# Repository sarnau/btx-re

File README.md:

# btx-re — Commodore BTX Decoder II firmware reverse engineering

Reconstructs a commented, byte-identical assembly listing of the Commodore
Bildschirmtext Decoder II ROM (`c64_btx_decoder_ii.bin`, MC6801, 32 KB at
`$8000`–`$FFFF`).

## Usage

    python3 build.py            regenerate out/btx_decoder_ii.asm and verify
    python3 build.py --check    verify without writing
    python3 build.py --report   show unresolved jumps and unreached regions
    python3 -m pytest           run the test suite

## How to work on this

`out/btx_decoder_ii.asm` is **generated**. Never edit it. All analysis goes into
`sidecar/decoder_ii.toml`:

| Section | Purpose |
|---|---|
| `entry_points` | Code entry addresses. Add the target of every computed jump you resolve. |
| `labels` | Address → symbol name. Used for branch targets and extended operands. |
| `line_comments` | Address → a note. Prints under the label on a labelled address, trailing otherwise. |
| `block_comments` | Address → multi-line banner above that address. |
| `symbols` | Address → name for hardware registers and RAM locations. |
| `regions` | Typed data ranges: `bytes`, `words`, `words_raw`, `string`, `ptr_table`, `chargen`, `code6502`, `petscii`, `byte_word`. `words` resolves names, `ptr_table` also allows offsets, `words_raw` is values and resolves nothing. |
| `c64_blocks` | 6502 blocks: ROM range plus the address each runs at on the C64. |
| `c64_symbols` | Names for the BTX register window as the C64 sees it. |
| `c64_pointers` | Zero-page pairs the payload loads as a 16-bit address. |
| `site_symbols` | Instruction address → operand name, for a location the firmware reuses. `$048E` is a mask, an index and a fill value in three routines, so the name is attached to the site. |
| `literal_immediates` | Instructions whose 16-bit immediate is a constant that collides with a named address — `LDX #$4000` is a parameter pair, not `planeRender`. |

`entry_points` must appear **above** the `[meta]` header. TOML assigns bare keys
written after a table header to that table, so putting it below silently makes it
`meta.entry_points` and yields an empty disassembly. The loader rejects that case
explicitly.

After every change, run `python3 build.py`. It must print
`OK         reassembles byte-identical`. If it does not, stop and fix that before
doing anything else — a broken round-trip means the listing no longer describes
the ROM.

Use `--report` to find the next thing to work on: unresolved computed jumps are
where code coverage is being lost, and the largest unreached regions are either
undiscovered code or data that needs a region entry.

The package was originally `dis6801`, renamed to `dis65xx` once the embedded
6502 payload was identified and the toolchain grew a second instruction set.
The design spec and plan under `docs/superpowers/` were updated to match, so
their paths point at real files.

## Two instruction sets, two sources

The image holds a C64-side 6502 program as well as the 68B01 firmware. They are
kept in **separate sources**, because the two live in different address spaces
and mixing them made every operand a special case.

Each 6502 block is assembled on its own at the address it really runs at, and
the result is linked back into the 6801 listing as binary:

    out/c64_bootstrap.asm   ORG $8000   ->  c64_bootstrap.bin    121 bytes
    out/c64_payload.asm     ORG $0FFE   ->  c64_payload.bin     7523 bytes
    out/btx_decoder_ii.asm  ORG $8000   ->  BINCLUDEs both      32768 bytes

The payload starts at the PRG load-address word and is ORGed two bytes early so
its data still lands at $1000. `c64_payload.bin` is therefore a genuine C64
`.prg` - load address followed by data - which is exactly what the 6801 streams
and what the bootstrap's loader consumes. The two blocks are contiguous, so the
6801 listing carries nothing but the two BINCLUDEs.

PETSCII text uses a `petscii` region kind. The C64 lowercase charset puts
uppercase at `$C1-$DA` and lowercase at `$41-$5A`, so the emitter brackets such
a region with `CHARSET` and writes the text as ordinary letters - which is how
`C2 49 4C 44 ...` becomes `"Bildschirmtext"` rather than a hex dump.

Hardware the C64 sees is symbolic too: `btxRxWr`, `btxRxRd`, `btxXferEn`
and friends are declared under `c64_symbols` in the sidecar and pair with the
6801-side names at `$6000`.

`build.py` checks each block against the ROM bytes it came from before the 6801
listing pulls it in, so a failure says which block broke rather than giving one
offset in a 32 KB image.

The payoff is that neither listing carries the other's quirks. The 6801 listing
is pure 6801 with a single `CPU` directive. The 6502 sources sit at their real
addresses, so every target is an ordinary label - no EQU indirection, no
cross-reference comments - and C64 ROM entry points are named
(`dis65xx/c64kernal.py`) rather than given `L<addr>` forms that would collide
with 6801 listing labels.

Which ROM range is which block, and where it runs, is declared in the sidecar
under `c64_blocks`.

## Labels

Every branch and jump target is a label. Targets the sidecar has named keep that
name; the rest get `L<address>`. Nothing branches to a bare address in either
listing.

## Why not Ghidra

Ghidra ships no 6800/6801 processor module. Its `MC6800/data/languages/6800.ldefs`
defines only 6809 and H6309, and lists `6800`/`6801`/`6803`/`6808` merely as
IDA-Pro import aliases mapped onto the **6809** module — a different opcode map.
Ghidra would produce plausible-looking but wrong disassembly.

## Layout

    dis65xx/opcodes.py     MC6801 opcode table (pure data)
    dis65xx/decode.py      bytes -> one 6801 instruction
    dis65xx/encode.py      one 6801 instruction -> bytes
    dis65xx/opcodes6502.py NMOS 6502 opcode table (151 documented opcodes)
    dis65xx/codec6502.py   6502 decode and encode
    dis65xx/trace.py     recursive-descent code discovery
    dis65xx/emit.py      code/data map + sidecar -> listing text
    dis65xx/asm.py       listing text -> bytes (the round-trip verifier)
    dis65xx/sidecar.py   analysis metadata loading
    tools/report.py      unresolved jumps and coverage gaps
    tools/checkdoc.py    docs against the generated sources
    tools/showfont.py    render a character set
    tools/diffrom.py     compare the two ROM revisions
    build.py             regenerate, assemble, compare, report

    c64_btx_decoder_ii.bin                     the ROM this project reads
    c64_BTX_decoder_CV30113 C375-B1-1 (EX).BIN the other revision
    third_party/         asl and c64rom sources, see third_party/README.md
    PDFs/                datasheets and specifications, see below
    other/               third-party BTX material, see below
    prior-analysis/      an earlier IDA pass, see prior-analysis/README.md

Both ROM images live in this repository, so nothing here depends on a path
outside it. `sidecar/decoder_ii.toml` names the primary one under `meta.rom`
and pins it by SHA-256, which is what makes a swapped or truncated image a
build failure rather than a silently different disassembly.

`PDFs/` holds the primary sources the architecture document reasons from: the
MC6801 reference manual and datasheet, ETS 300 072 for CEPT, Commodore's
*Bedienungshandbuch* for this cartridge, and datasheets for the parts on the board —
the 65005 gate array, the MC1377 encoder, the M41464 DRAMs, and the handful of
74-series glue chips. They are the reason a claim about the hardware can be
checked against something other than the ROM.

`other/` is third-party BTX material kept for reference, not built by anything
here: a small BTX server in JavaScript with a page set, and the 2015
*Bildschirm Trix* distribution — the mikroPAD and miniBTX terminal projects
with their schematics, a CEPT decoder, documentation and photographs. These
describe modern recreations rather than Commodore's cartridge, so they inform
the CEPT side of this work but do not answer the open hardware questions about
the Decoder II itself.

Three archives in `other/` are deliberately untracked, listed in `.gitignore`
and roughly 113 MB in total. Committing them is effectively irreversible, since
they stay in the history forever, whereas adding them later is trivial.

`conftest.py` at the repository root is load-bearing: its presence is what puts
the repository root on `sys.path` for pytest. Deleting it breaks every test.

See `docs/superpowers/specs/2026-08-17-c64-btx-decoder-re-design.md` for the design.

## Documents

- `docs/btx-decoder-ii-architecture.md` - how the module works
- `docs/cv30113-revision-diff.md` - the two ROM revisions compared
- `docs/superpowers/specs/` - the original design spec and plan

## Current state

Bootstrap trace from the reset vector and the seven interrupt stubs classifies
25% of the image, with 12 unresolved computed jumps and no decode failures.
`$8000`–`$9FFF` is character-generator bitmap data; the `$D374`–`$D3E3` cluster
of computed jumps looks like table dispatch and is the obvious next target.

## Independent verification

`tools/check_asl.sh` reassembles the generated listing with asl (Macro Assembler
AS) and compares the result against the ROM. `dis65xx/asm.py` shares an opcode
table with the disassembler, so a wrong entry round-trips cleanly through both;
asl does not share it, which is what makes it worth running. It has caught real
errors — that `DW` follows the target's endianness on a 6801, and four cases
where `asm.py` accepted syntax asl rejects.

asl is not in Homebrew and its source URL is unversioned, so a copy lives in
`third_party/`. If asl is not on PATH the script builds it from there, once,
into `third_party/build/` — which means the cross-check needs no network and no
setup:

    ./tools/check_asl.sh

To use an asl you built yourself instead:

    ASL=/path/to/asl P2BIN=/path/to/p2bin AS_MSGPATH=/path/to/asl-current \
        ./tools/check_asl.sh

Exit code 77 means asl was neither on PATH nor buildable, and the check was
skipped rather than silently passing.

Status: **passing** — asl assembles the listing with 0 errors and 0 warnings and
its output is byte-identical to the ROM, independently confirming the opcode table.

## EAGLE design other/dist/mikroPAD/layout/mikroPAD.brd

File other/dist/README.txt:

B I L D S C H I R M   T R I X
                   =================================
                    Vintage Computing Festival 2015
                                Edition

Preface
==========================

During my time travel through the lost computerworld I came across
"Bildschirmtext", an information system based on a technology called
"Videotex". Videotex looks similar to the Teletext system you know
well from your TV-Set. However. Videotex has some extra capabilities.
It is an interactive medium that allows direct interaction with a 
computersystem. It has limited graphic capabilites. A user can define
own character tiles and custom colors. With some tricks even 
animations are possible. I find Videotex an exciting and beautiful
media.

Today the entire videotex-world with all its colorful, pixelized 
information pages is lost. Everything is gone. However, here and
there one can find some leftover Terminals. How sad, I thought,
but what if we could create a new backhaul for these?

I started researching the Interface, got the ETSI-Specifications and
after a few month I had my own videotex-backhaul running. This 
package contains the outcome of my research and everything you need
to start an own CEPT TCD 6-1/ETS 300 072 videotex-service.

This disribution includes:
==========================

1) ./doc	(Some Documentation, download ETSI specs yourself)
2) ./gcc	The avr-gcc compiler needed to compile the microPAD 
                firmware
3) ./mikroPAD	A modern ip-modem version of the dbt03
4) ./miniBTX	An adapter to connect any dbt03 compatible terminal
                to your PC
		(Also includes some software tools)
5) ./pcPAD	The mikroPAD as a PC software for use with miniBTX
6) ./srv	A bunch of Videotex-Pages to start off
7) ./tools	Some tools to help you athoring own Videotex-Pages

Copyright / License
==========================

This is an open-source project. The entire system with its hardware
and software falls under the GNU General Public License (See
LICENSE.txt for details)

However, for the Videotex-Pages in ./srv do not fall under GPL.
Here I make the following exception: All my Videotex-Pages are
public domain. I will not claim any copyright for this work,
you can freely copy and edit the pages and create a new
beautiful artwork from it. 

If you still have Bildschirmtext content somewhere you wish to
donate you can contact me via email. Send me whatever you have,
diskettes, old backups, screenshots. I will then see if I have 
the time to restore the content. 

Contact
==========================

If you use some of my BTX work for your own projects. I would like
to hear from you. Feel free to ask me questions. I would love to 
see other enthusiasts working on videotex-projects.

Email: philipp.maier@runningserver.com

02082015 Philipp Fabian Benedikt Maier

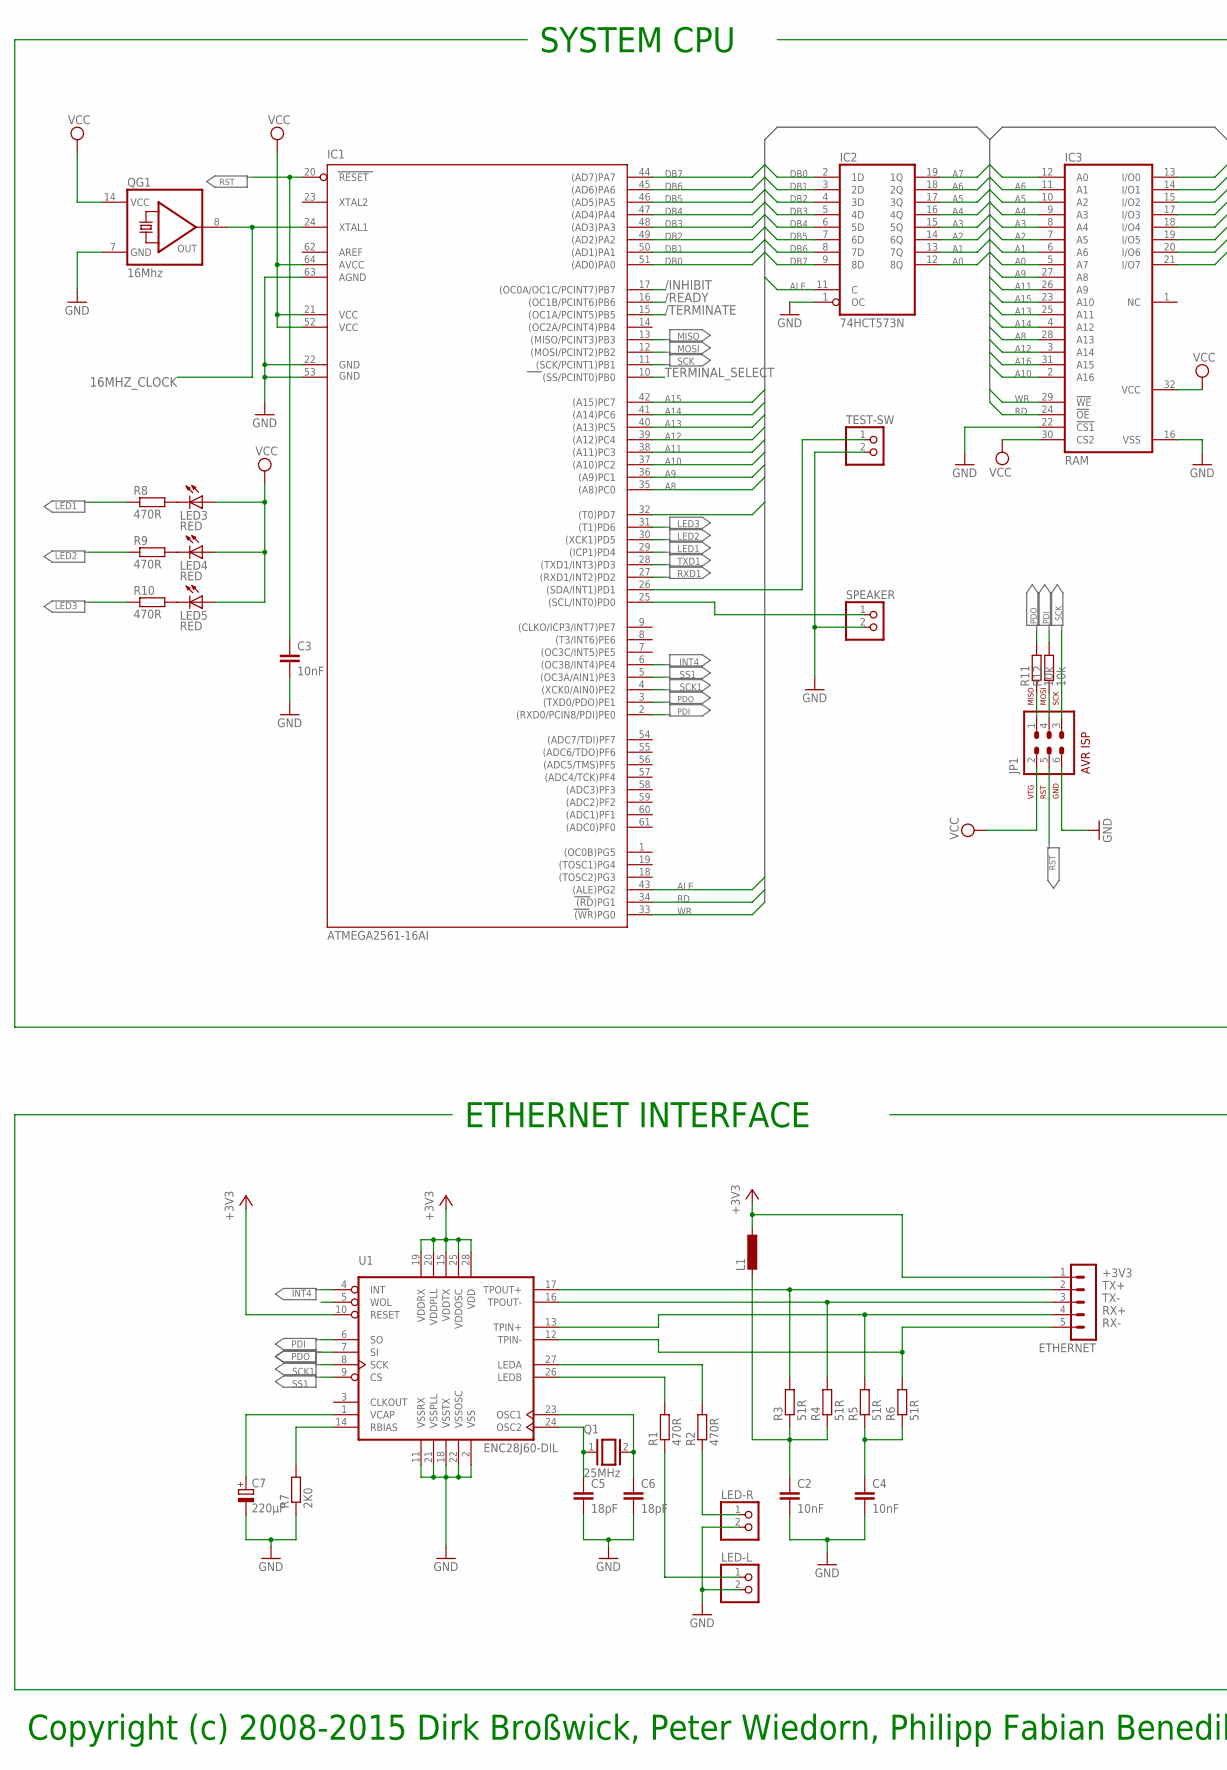
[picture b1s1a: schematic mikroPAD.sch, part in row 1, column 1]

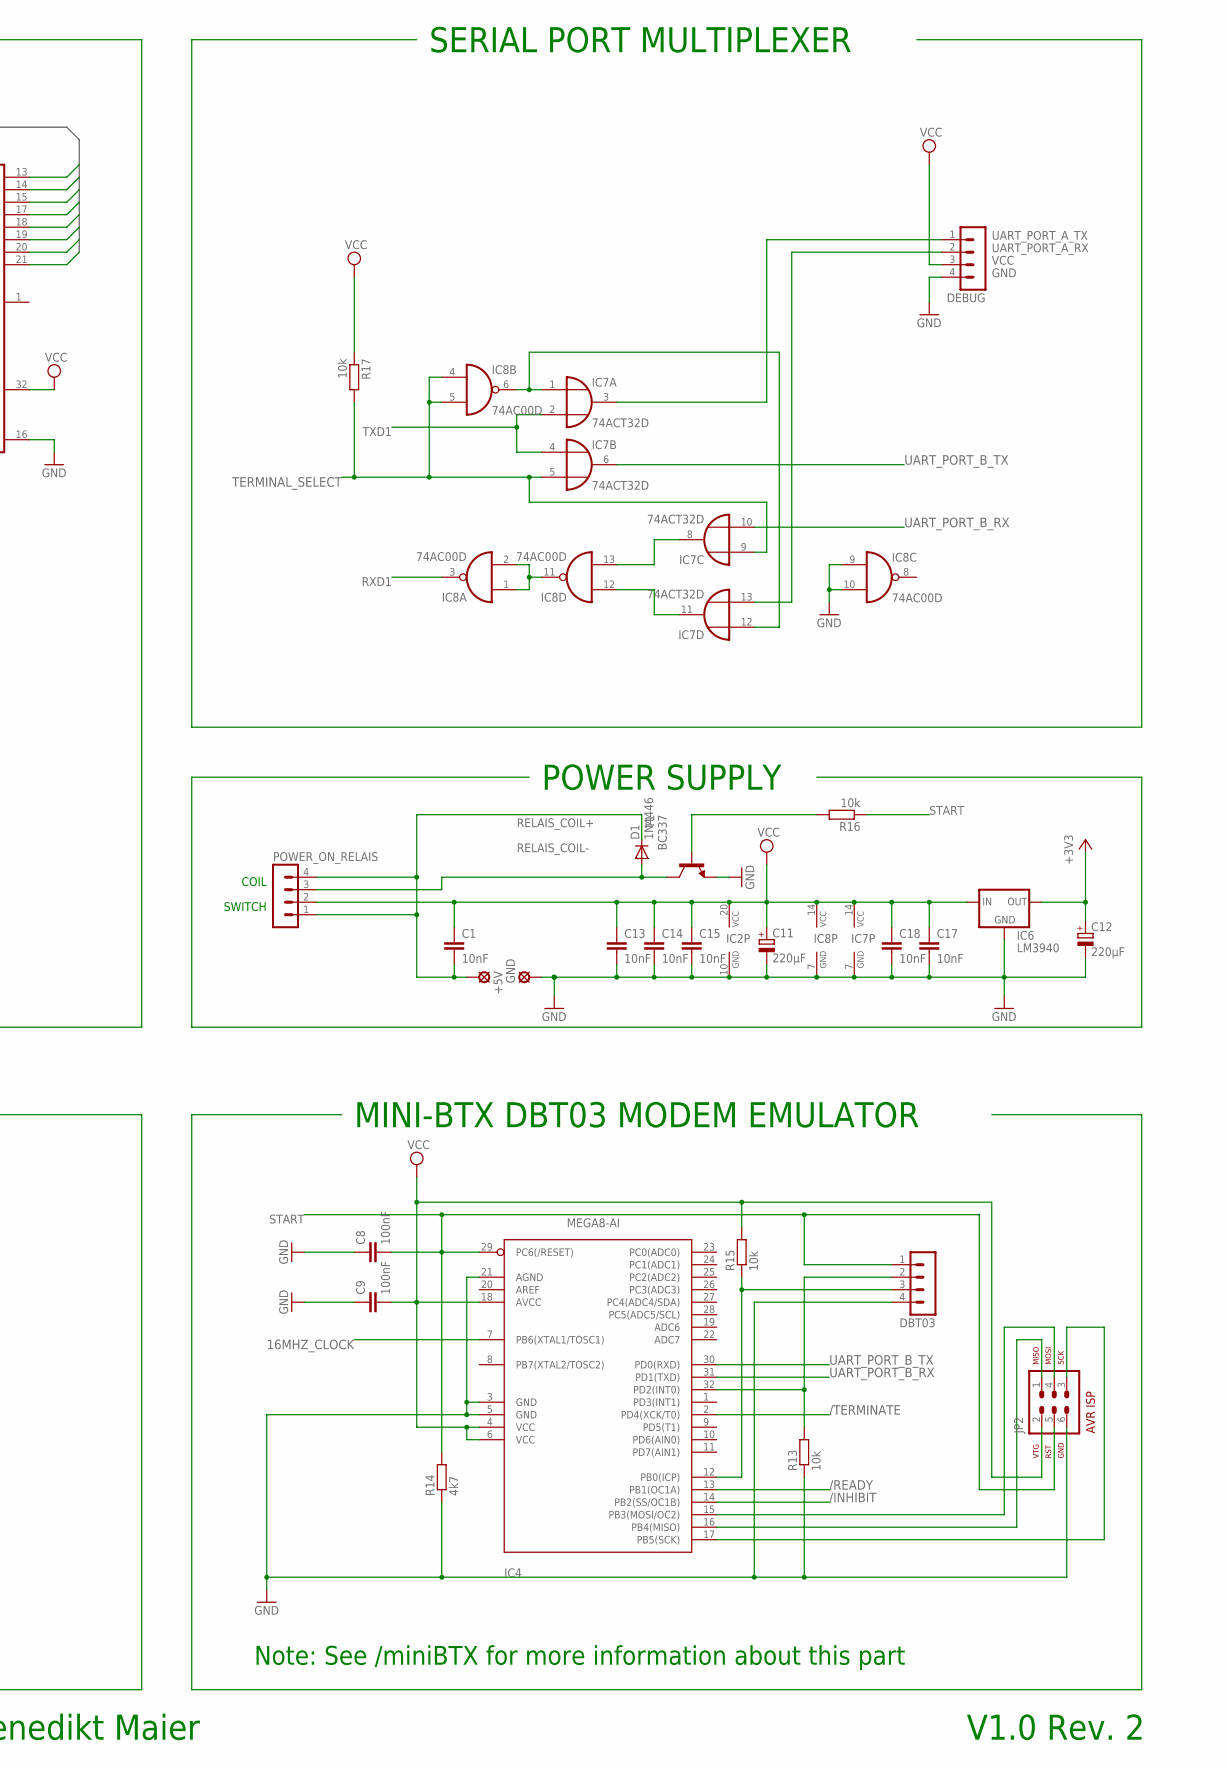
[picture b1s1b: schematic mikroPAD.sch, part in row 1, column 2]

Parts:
+5V: SE14
C1, C3, C13, C14, C15, C17, C18: 10nF; C025-025X050
C2, C4: 10nF; C025-030X050
C5, C6: 18pF; C025-025X050
C7: 220µF; E2-5
C8, C9: 100nF; C025-025X050
C11, C12: 220µF; E2,5-7
D1: 1N4446; DO35-10
DBT03: MA04-1
DEBUG: MA04-1
ETHERNET: MA05-1
GND: SE14
IC1: ATMEGA2561-16AI; TQFP64
IC2: 74HCT573N; DIL20
IC3: RAM; DIL32
IC4: MEGA8-AI; TQFP32-08
IC6: LM3940; 78XXS
IC7: 74ACT32D; SO14
IC8: 74AC00D; SO14
JP1, JP2: AVR-ISP-6
L1: L-EU0207/10; 0207/10
LED3, LED4, LED5: RED; LED3MM
LED-L: PINHD-1X2; 1X02
LED-R: PINHD-1X2; 1X02
POWER_ON_RELAIS: MA04-1
Q1: 25MHz; QS
QG1: 16Mhz; DIL14S
R1, R2, R8, R9, R10: 470R; 0207/10
R3, R4, R5, R6: 51R; 0207/10
R7: 2K0; 0207/10
R11, R12, R13, R15: 10k; 0204/5
R14: 4k7; 0204/5
R16: 10k; 0207/12
R17: 10k; 0204/7
SPEAKER: PINHD-1X2; 1X02
T1: BC337; TO92
TEST-SW: PINHD-1X2; 1X02
U1: ENC28J60-DIL; DIL28-3

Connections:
16MHZ_CLOCK: IC1.24 (XTAL1), IC4.7 (PB6(XTAL1/TOSC1)), QG1.8 (OUT)
+3V3: C12.+, ETHERNET.1, IC6.OUT, L1.1, U1.10 (RESET), U1.15 (VDDTX), U1.19 (VDDRX), U1.20 (VDDPLL), U1.25 (VDDOSC), U1.28 (VDD)
/INHIBIT: IC1.17 ((OC0A/OC1C/PCINT7)PB7), IC4.14 (PB2(SS/OC1B))
/READY: IC1.16 ((OC1B/PCINT6)PB6), IC4.13 (PB1(OC1A))
/TERMINATE: IC1.15 ((OC1A/PCINT5)PB5), IC4.2 (PD4(XCK/T0))
A0: IC2.12 (8Q), IC3.5 (A7)
A1: IC2.13 (7Q), IC3.6 (A6)
A2: IC2.14 (6Q), IC3.7 (A5)
A3: IC2.15 (5Q), IC3.8 (A4)
A4: IC2.16 (4Q), IC3.9 (A3)
A5: IC2.17 (3Q), IC3.10 (A2)
A6: IC2.18 (2Q), IC3.11 (A1)
A7: IC2.19 (1Q), IC3.12 (A0)
A8: IC1.35 ((A8)PC0), IC3.28 (A13)
A9: IC1.36 ((A9)PC1), IC3.27 (A8)
A10: IC1.37 ((A10)PC2), IC3.2 (A16)
A11: IC1.38 ((A11)PC3), IC3.26 (A9)
A12: IC1.39 ((A12)PC4), IC3.3 (A14)
A13: IC1.40 ((A13)PC5), IC3.25 (A11)
A14: IC1.41 ((A14)PC6), IC3.4 (A12)
A15: IC1.42 ((A15)PC7), IC3.23 (A10)
A16: IC1.32 ((T0)PD7), IC3.31 (A15)
ALE: IC1.43 ((ALE)PG2), IC2.11 (C)
DB0: IC1.51 ((AD0)PA0), IC2.2 (1D), IC3.15 (I/O2)
DB1: IC1.50 ((AD1)PA1), IC2.3 (2D), IC3.14 (I/O1)
DB2: IC1.49 ((AD2)PA2), IC2.4 (3D), IC3.13 (I/O0)
DB3: IC1.48 ((AD3)PA3), IC2.5 (4D), IC3.17 (I/O3)
DB4: IC1.47 ((AD4)PA4), IC2.6 (5D), IC3.18 (I/O4)
DB5: IC1.46 ((AD5)PA5), IC2.7 (6D), IC3.19 (I/O5)
DB6: IC1.45 ((AD6)PA6), IC2.8 (7D), IC3.20 (I/O6)
DB7: IC1.44 ((AD7)PA7), IC2.9 (8D), IC3.21 (I/O7)
DBT03_RX: DBT03.2, IC4.32 (PD2(INT0)), R13.2
DBT03_TX: DBT03.3, IC4.12 (PB0(ICP)), R15.1
GND: C2.2, C3.2, C4.2, C5.2, C6.2, C7.-, C8.1, C9.1, C11.-, C12.-, C13.2, C14.2, C15.2, C17.2, C18.2, DBT03.4, DEBUG.4, GND.MP, IC1.22 (GND), IC1.53 (GND1), IC1.63 (AGND), IC2.1 (OC), IC2.10 (GND), IC3.16 (VSS), IC3.22 (!CS1), IC4.3 (GND), IC4.5 (GND), IC4.21 (AGND), IC6.GND, IC7.7 (GND), IC8.7 (GND), IC8.9 (I0), IC8.10 (I1), JP1.6, JP2.6, LED-L.2, LED-R.2, QG1.7 (GND), R7.1, R13.1, R14.1, SPEAKER.2, T1.1 (E), TEST-SW.2, U1.2 (VSS), U1.11 (VSSRX), U1.18 (VSSTX), U1.21 (VSSPLL), U1.22 (VSSOSC)
INT4: IC1.6 ((OC3B/INT4)PE4), U1.4 (INT)
LED1: IC1.29 ((ICP1)PD4), R8.1
LED2: IC1.30 ((XCK1)PD5), R9.1
LED3: IC1.31 ((T1)PD6), R10.1
LEDA: R2.2, U1.27 (LEDA)
LEDA_: LED-R.1, R2.1
LEDB: R1.2, U1.26 (LEDB)
LEDB_: LED-L.1, R1.1
MISO: IC1.13 ((MISO/PCINT3)PB3)
MOSI: IC1.12 ((MOSI/PCINT2)PB2)
unnamed: LED3.K (C), R8.2
unnamed: LED4.K (C), R9.2
unnamed: LED5.K (C), R10.2
unnamed: R16.2, T1.2 (B)
unnamed: C5.1, Q1.1, U1.24 (OSC2)
unnamed: C4.1, R5.1, R6.1
unnamed: C2.1, L1.2, R3.1, R4.1
unnamed: C6.1, Q1.2, U1.23 (OSC1)
unnamed: R7.2, U1.14 (RBIAS)
unnamed: C7.+, U1.1 (VCAP)
unnamed: IC8.1 (I0), IC8.2 (I1), IC8.11 (O)
unnamed: JP1.1, R11.1
unnamed: JP1.4, R12.1
unnamed: IC7.8 (O), IC8.13 (I1)
unnamed: IC7.1 (I0), IC7.12 (I0), IC8.6 (O)
unnamed: IC7.11 (O), IC8.12 (I0)
unnamed: IC4.17 (PB5(SCK)), JP2.3
unnamed: IC4.15 (PB3(MOSI/OC2)), JP2.4
unnamed: IC4.16 (PB4(MISO)), JP2.1
OC2A: IC1.26 ((SDA/INT1)PD1), TEST-SW.1
PDI: IC1.2 ((RXD0/PCIN8/PDI)PE0), R12.2, U1.6 (SO)
PDO: IC1.3 ((TXD0/PDO)PE1), R11.2, U1.7 (SI)
RD: IC1.34 ((RD)PG1), IC3.24 (!OE)
RELAIS_COIL+: +5V.MP, C1.2, D1.C, POWER_ON_RELAIS.1, POWER_ON_RELAIS.4
RELAIS_COIL-: D1.A, POWER_ON_RELAIS.3, T1.3 (C)
RST: C3.1, IC1.20 (RESET), JP1.5
RX+: ETHERNET.4, R5.2, U1.13 (TPIN+)
RX-: ETHERNET.5, R6.2, U1.12 (TPIN-)
RXD1: IC1.27 ((RXD1/INT2)PD2), IC8.3 (O)
SCK: IC1.11 ((SCK/PCINT1)PB1), JP1.3
SCK1: IC1.4 ((XCK0/AIN0)PE2), U1.8 (SCK)
SPEAKER: IC1.25 ((SCL/INT0)PD0), SPEAKER.1
SS1: IC1.5 ((OC3A/AIN1)PE3), U1.9 (CS)
START: C8.2, DBT03.1, IC4.29 (PC6(/RESET)), JP2.5, R14.2, R16.1
TERMINAL_SELECT: IC1.10 ((SS/PCINT0)PB0), IC7.5 (I1), IC7.9 (I0), IC8.4 (I0), IC8.5 (I1), R17.2
TX+: ETHERNET.2, R3.2, U1.17 (TPOUT+)
TX-: ETHERNET.3, R4.2, U1.16 (TPOUT-)
TXD1: IC1.28 ((TXD1/INT3)PD3), IC7.2 (I1), IC7.4 (I0)
UART_PORT_A_RX: DEBUG.2, IC7.13 (I1)
UART_PORT_A_TX: DEBUG.1, IC7.3 (O)
UART_PORT_B_RX: IC4.31 (PD1(TXD)), IC7.10 (I1)
UART_PORT_B_TX: IC4.30 (PD0(RXD)), IC7.6 (O)
VCC: C1.1, C9.2, C11.+, C13.1, C14.1, C15.1, C17.1, C18.1, DEBUG.3, IC1.21 (VCC), IC1.52 (VCC1), IC1.64 (AVCC), IC2.20 (VCC), IC3.30 (CS2), IC3.32 (VCC), IC4.4 (VCC), IC4.6 (VCC), IC4.18 (AVCC), IC6.IN, IC7.14 (VCC), IC8.14 (VCC), JP1.2, JP2.2, LED3.A, LED4.A, LED5.A, POWER_ON_RELAIS.2, QG1.14 (VCC), R15.2, R17.1
WOL: U1.5 (WOL)
WR: IC1.33 ((WR)PG0), IC3.29 (!WE)

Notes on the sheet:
SYSTEM CPU
SERIAL PORT MULTIPLEXER
POWER SUPPLY
MINI-BTX DBT03 MODEM EMULATOR
Note: See /miniBTX for more information about this part
ETHERNET INTERFACE
SWITCH
COIL
Copyright (c) 2008-2015 Dirk Broßwick, Peter Wiedorn, Philipp Fabian Benedikt Maier
V1.0 Rev. 2

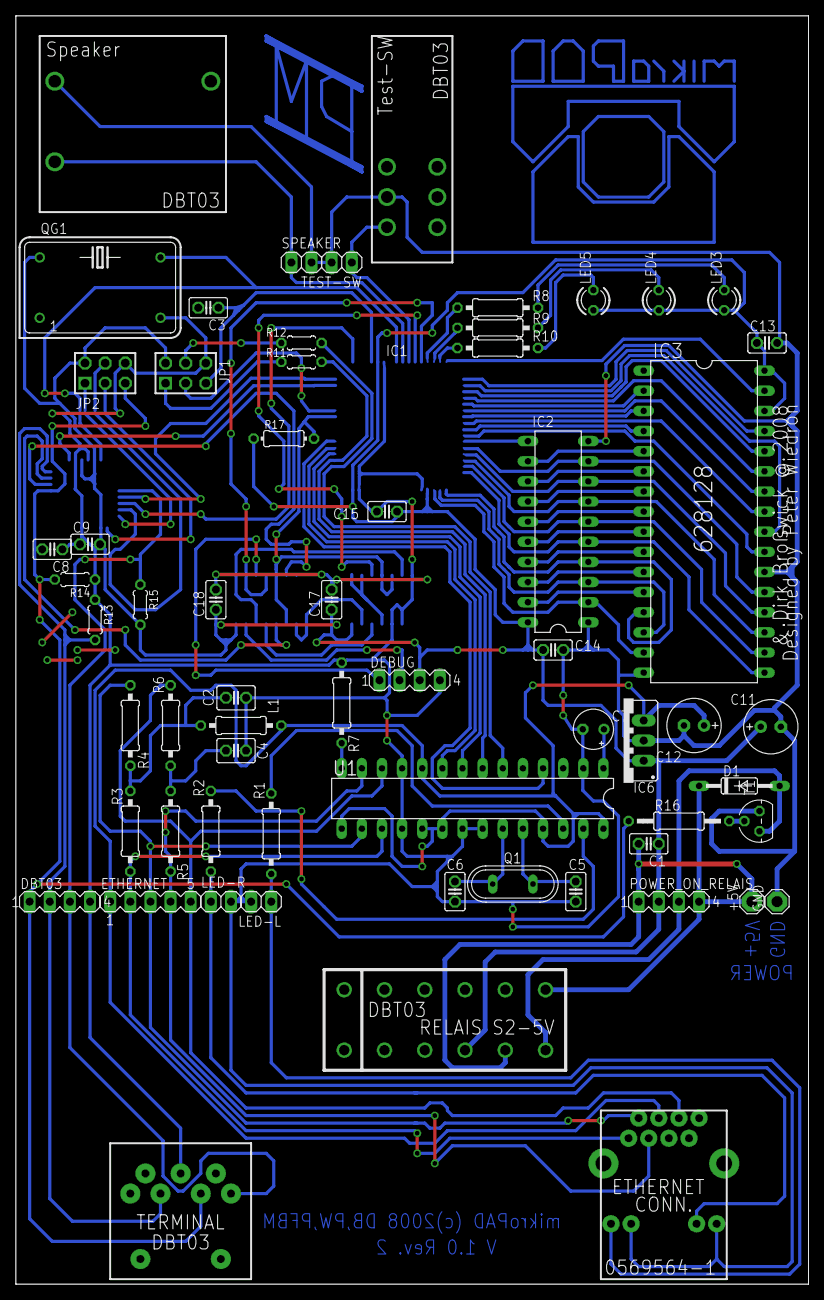
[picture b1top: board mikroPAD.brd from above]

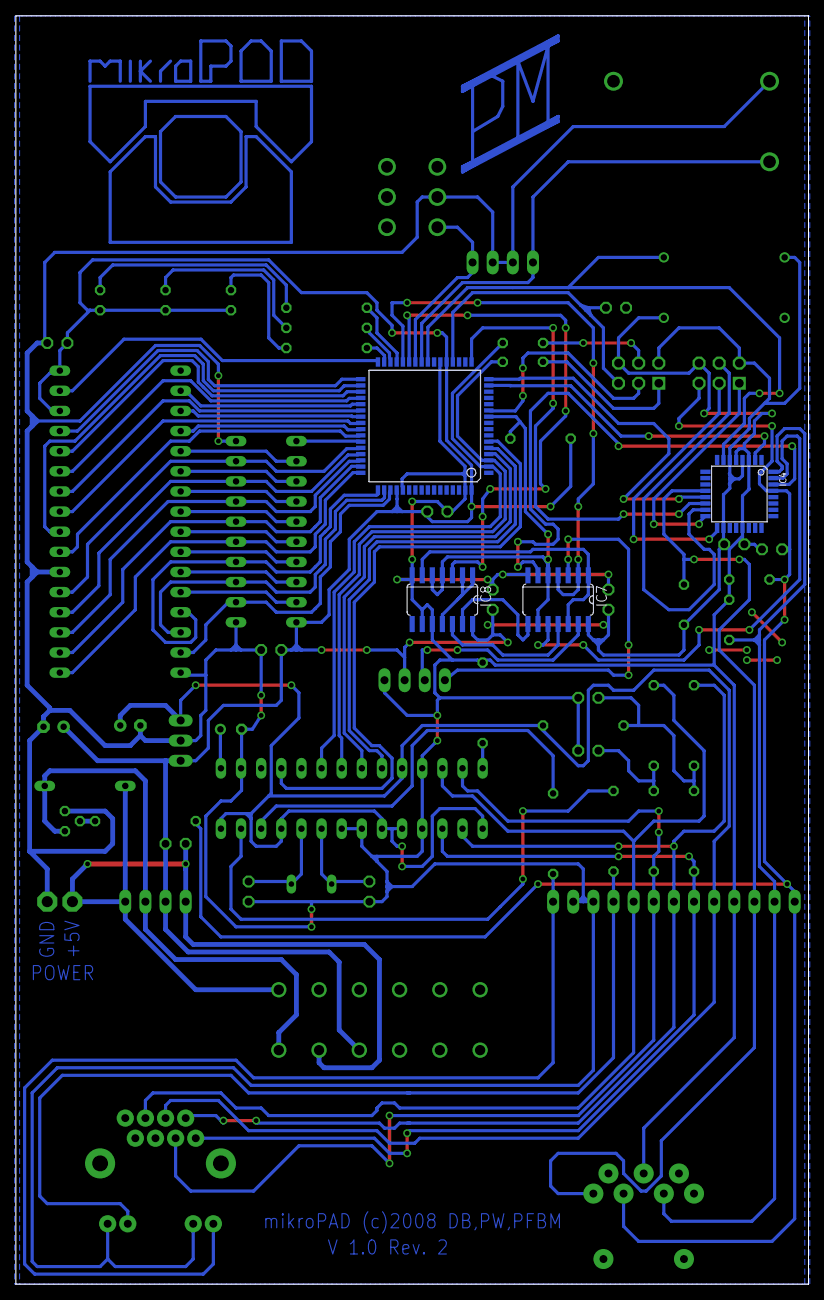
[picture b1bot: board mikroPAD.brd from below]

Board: 2 copper layers, 100.0 x 160.0 mm, 61 parts (4 on the bottom side), 86 nets.

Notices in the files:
other/dist/mikroPAD/layout/mikroPAD.brd:
mikroPAD (c)2008 DB,PW,PFBM
